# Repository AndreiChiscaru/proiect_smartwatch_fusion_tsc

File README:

# InkTime - Open Source Smartwatch 

Acest repository conține fișierele de design hardware (faza EVT) pentru **InkTime**, un smartwatch accesibil și open-source, bazat pe microcontrolerul nRF52840. Proiectul a fost dezvoltat de la specificații la PCB asamblat, incluzând schema electrică, design-ul plăcii și integrarea componentelor mecanice în carcasa 3D personalizată.

---

## 1. Diagrama Bloc a Sistemului

*(Notă: Arhitectura de bază folosește nRF52840 ca unitate centrală, comunicând periferic cu senzorii și display-ul, având un management de putere dedicat.)*

---

## 2. Descrierea Funcționalității Hardware

Sistemul este construit în jurul SoC-ului **nRF52840**, ales pentru conectivitatea Bluetooth Low Energy (BLE) și eficiența energetică excelentă.

**Module și Interfețe Integrate:**
* **Display E-Paper:** Conectat la microcontroler prin interfața **SPI** (MOSI, SCK, CS), asigurând un consum extrem de redus de energie, consumând curent doar în timpul refresh-ului ecranului.
* **IMU (Senzor de mișcare):** Pentru detecția gesturilor (ex. ridicarea mâinii). Comunică exclusiv prin interfața **I2C** (SDA, SCL).
* **Feedback Haptic (Shaker):** Un motor de vibrații controlat printr-un pin **PWM/GPIO**, utilizat pentru notificări silențioase.
* **Interfață Utilizator:** 3 butoane fizice tip push-button conectate cu rezistențe de pull-up interne.
* **Managementul Energiei:** * Sistemul este alimentat de o baterie Li-Po lipită direct pe pad-urile plăcii (fără conector JST) pentru a respecta constrângerea de spațiu pe axa Z.
  * Încărcarea se face prin portul **USB-C** folosind un circuit dedicat de management al bateriei.
  * Tensiunea este stabilizată la **3V3** printr-un convertor LDO/DC-DC pentru restul circuitelor.

---

## 3. Maparea Pinilor (nRF52840 Pinout)

Mai jos este prezentată alocarea pinilor pentru componentele periferice principale, optimizată pentru a minimiza încrucișările de trasee pe PCB:

| Componentă / Modul | Pini nRF52840 utilizați | Funcție / Interfață |
| :--- | :--- | :--- |
| **Display E-Paper** | P0.13, P0.15, P0.17, P0.20, P0.22 | SPI (SCK, MOSI, CS, DC, RST) |
| **Senzor IMU** | P0.26, P0.27 | I2C (SDA, SCL) |
| **Buton 1 (Up)** | P1.13 | GPIO (Input Pull-up) |
| **Buton 2 (Select)** | P1.14 | GPIO (Input Pull-up) |
| **Buton 3 (Down)** | P1.15 | GPIO (Input Pull-up) |
| **Motor Vibrații (Shaker)**| P0.11 | GPIO (Output / PWM) |
| **Monitorizare Baterie**| P0.02 | ADC (Analog In) |

---

## 4. Bill of Materials (BOM) Extras

Lista componentelor principale utilizate în acest design:

| Componentă | Capsulă / Pachet | Funcție | Link Achiziție / Datasheet |
| :--- | :--- | :--- | :--- |
| **nRF52840-QIAA-R** | QFN-73 | Microcontroler principal (SoC) | [JLC Parts](https://jlcpcb.com/parts) |
| **LSM6DS3TR** | LGA-14 | IMU (Accelerometru + Giroscop) | [JLC Parts](https://jlcpcb.com/parts) |
| **BQ24040DSQR** | WSON-8 | IC Management Încărcare Baterie | [JLC Parts](https://jlcpcb.com/parts) |
| **AP2112K-3.3** | SOT-23-5 | Regulator Tensiune 3.3V (LDO) | [JLC Parts](https://jlcpcb.com/parts) |
| **Conector FPC** | 24-pin, 0.5mm | Conector Display E-Paper | [JLC Parts](https://jlcpcb.com/parts) |
| **Pasive (C, R)** | 0201 / 0402 | Decuplare (100nF) și Pull-up (10k) | [JLC Parts](https://jlcpcb.com/parts) |

---

## 5. Design Log & Decizii de Proiectare (Issue-uri Acceptate)

Pentru a respecta cerințele tehnice și deadline-ul etapei EVT, au fost luate următoarele decizii de design:

* **Structura PCB:** Placa are **grosimea impusă de 1mm** și a fost realizată pe 2 layere (Top și Bottom). Amplasarea componentelor a fost făcută exclusiv pe layer-ul TOP. S-a realizat un plan de masă continuu pe ambele layere, unite prin via stitching.
* **Reguli de Rutare:** Liniile de alimentare (VCC, 3V3, VBAT, VUSB) au fost rutate manual respectând grosimea de **0.3mm**. Semnalele de date au folosit grosimea de **0.15mm**, evitându-se unghiurile drepte.
* **Zona RF:** Sub antena Bluetooth de 2.4GHz s-a aplicat Polygon Pour Cutout pe toate straturile. Nu există plan de masă sau trasee sub antenă, pentru a preveni ecranarea.
* **[BUG ACCEPTAT] Erori DRC și Acoperire Autorouter (89.2%):** Datorită densității masive de componente din jurul portului USB și a limitărilor mecanice foarte stricte impuse de carcasa 3D (mufele și butoanele au coordonate fixe), s-au acceptat temporar mici erori de tip *Overlap/Clearance* la condensatoarele 0201 aferente decuplării. Din același motiv de spațiu fizic limitat, Autorouter-ul a atins o acoperire maximă de 89.2%. Am decis să păstrez aceste câteva trasee nerutate pe Top în loc să mut componente pe Bottom, pentru a nu complica masiv viitorul proces de asamblare (Pick & Place pe ambele fețe crește mult costurile). Aceste conexiuni vor fi optimizate manual în sprint-ul pentru DVT.

---

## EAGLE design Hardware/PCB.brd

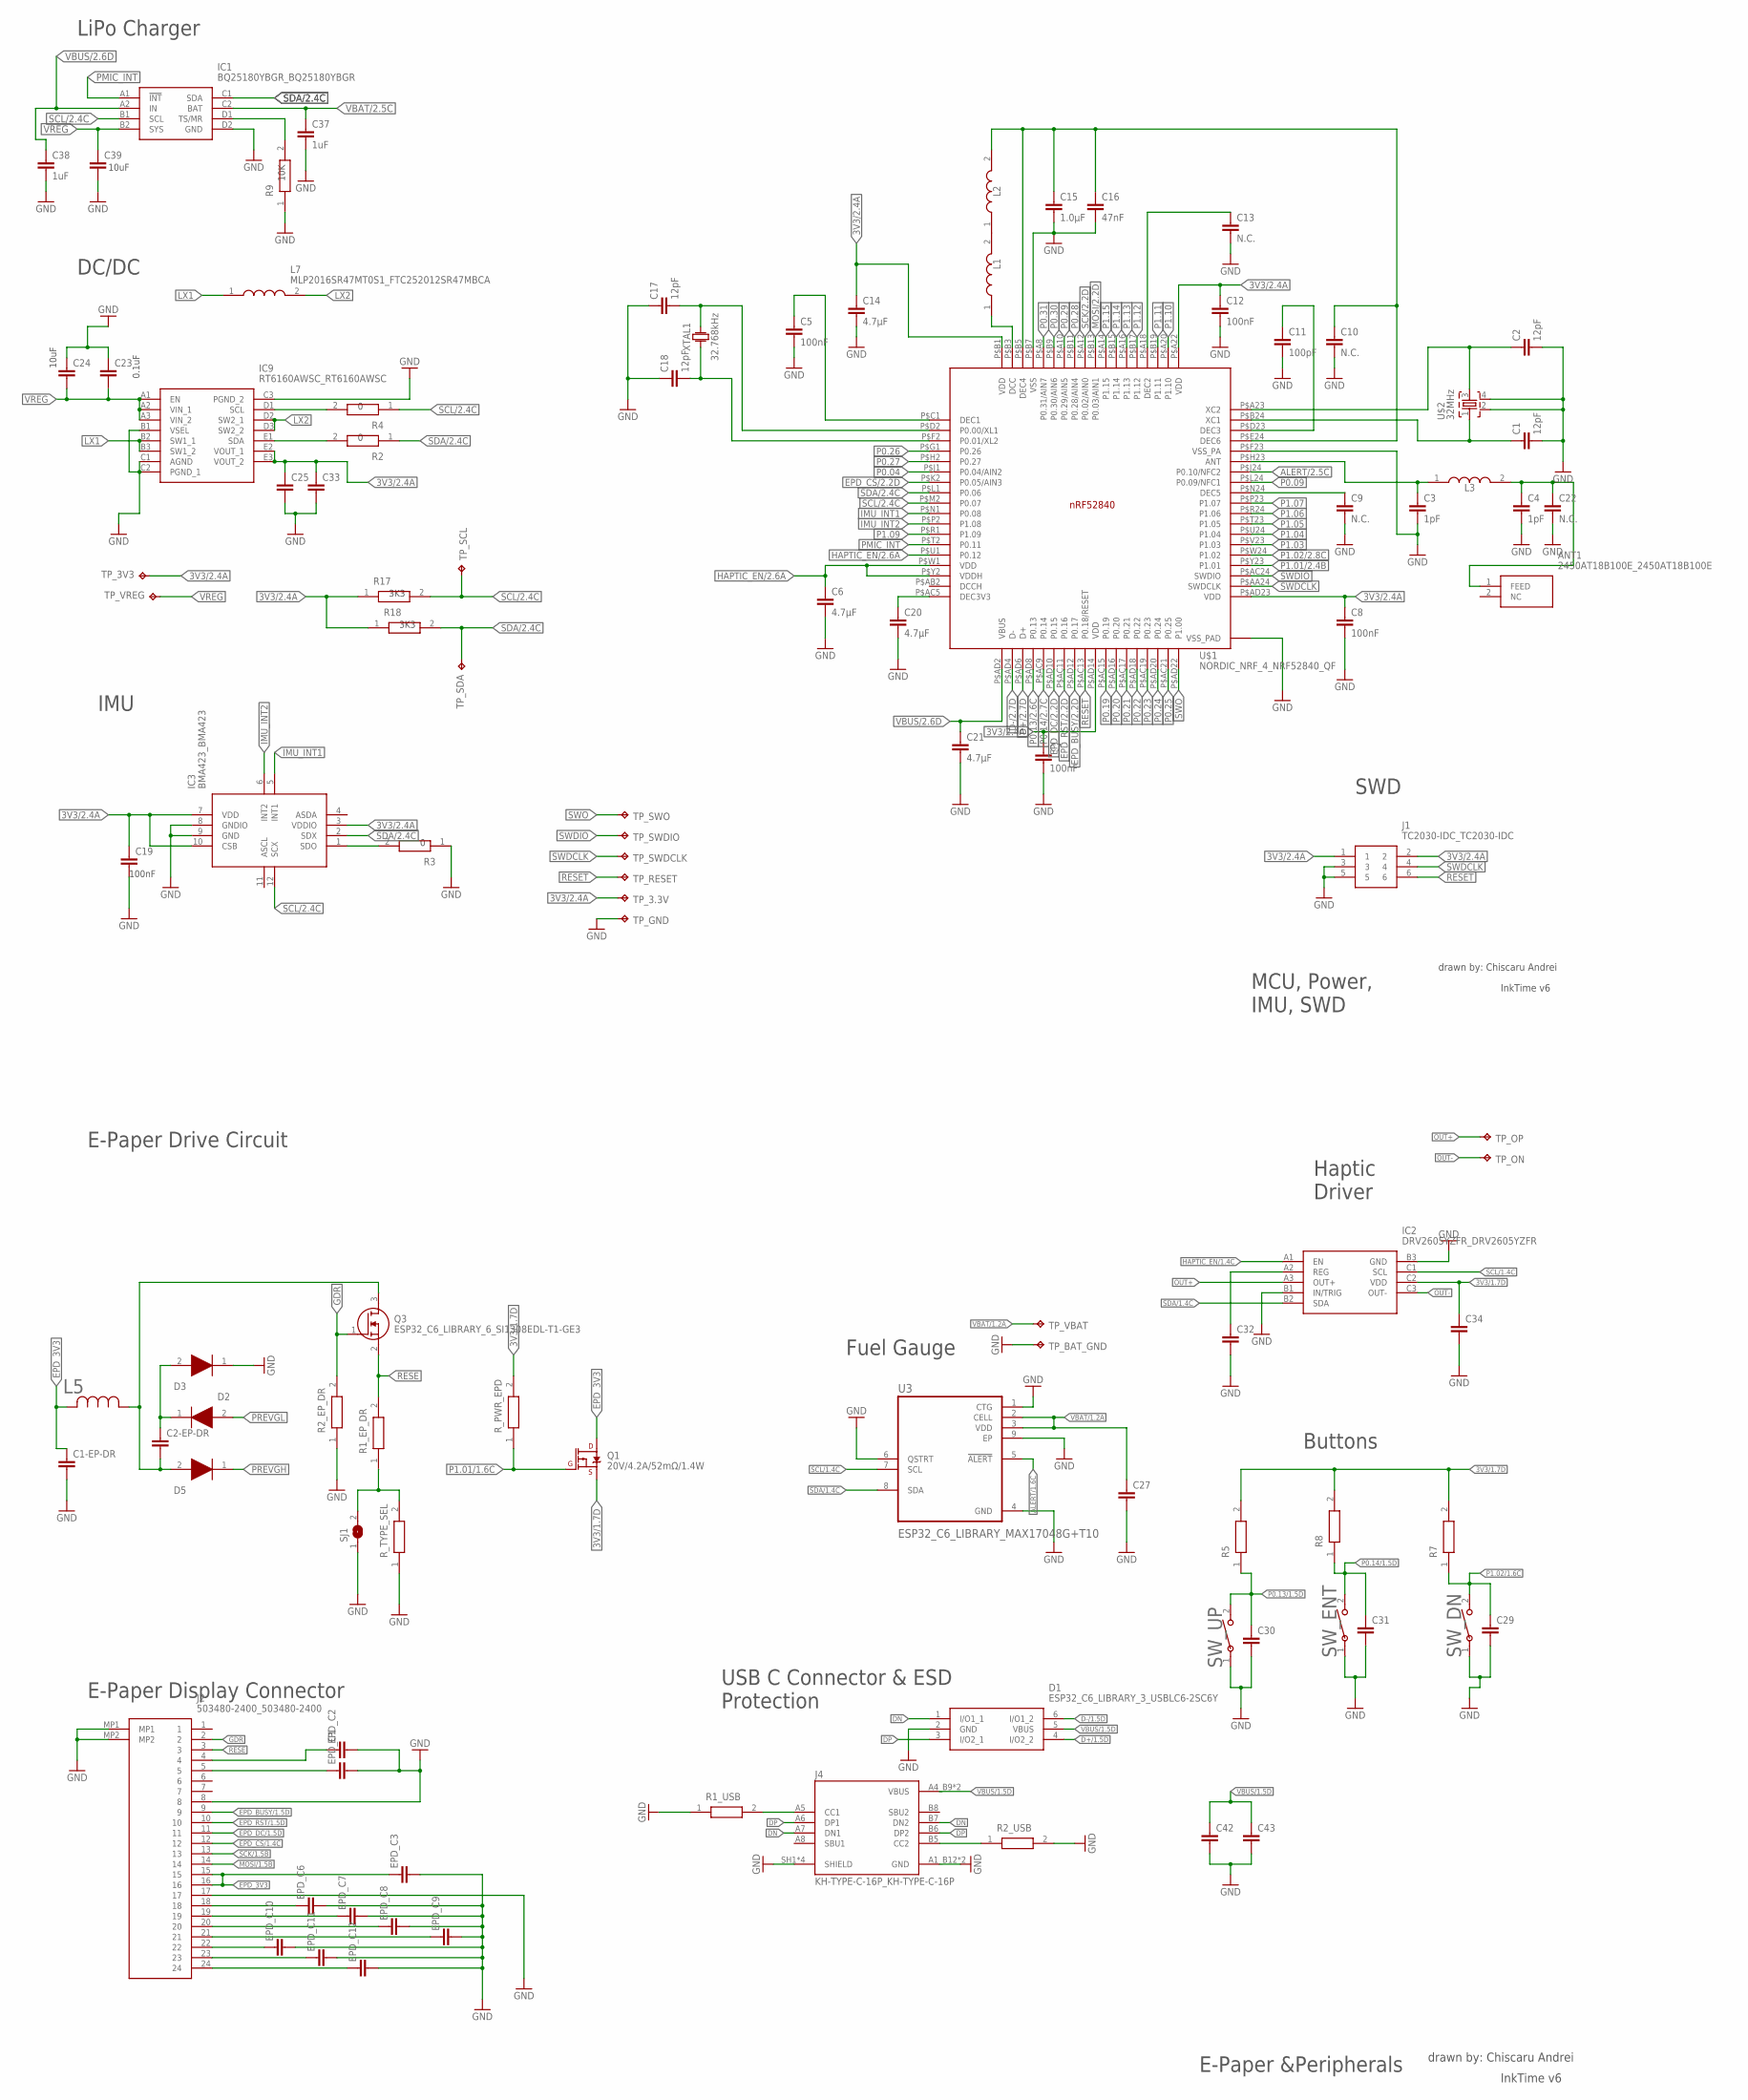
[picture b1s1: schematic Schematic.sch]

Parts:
ANT1: 2450AT18B100E_2450AT18B100E; 2450AT18B100E_ANTC3216X140N
C1, C2, C17, C18: 12pF; NORDIC_NRF_3_RESC0201_L
C1-EP-DR, C24, C39: 10uF; NORDIC_NRF_3_RESC0201_L
C2-EP-DR: 4.7uF/25V; NORDIC_NRF_3_RESC0201_L
C3, C4: 1pF; NORDIC_NRF_3_RESC0201_L
C5, C7, C8, C12, C19: 100nF; NORDIC_NRF_3_RESC0201_L
C6, C14, C20, C21: 4.7µF; NORDIC_NRF_3_RESC0201_L
C9, C10, C13, C22: N.C.; NORDIC_NRF_3_RESC0201_L
C11: 100pF; NORDIC_NRF_3_RESC0201_L
C15: 1.0µF; NORDIC_NRF_3_RESC0201_L
C16: 47nF; NORDIC_NRF_3_RESC0201_L
C23, C27, C34, C42: 0.1uF; NORDIC_NRF_3_RESC0201_L
C25, C33: 22uF; NORDIC_NRF_3_RESC0201_L
C29, C30, C31, C32, C37, C38: 1uF; NORDIC_NRF_3_RESC0201_L
C43: 4.7uF; NORDIC_NRF_3_RESC0201_L
D1: ESP32_C6_LIBRARY_3_USBLC6-2SC6Y; ESP32_C6_LIBRARY_3_SOT95P280X145-6N
D2, D3, D5: ESP32_C6_LIBRARY_5_MBR0530; ESP32_C6_LIBRARY_5_SOD3716X135N
EPD_C1, EPD_C2, EPD_C6, EPD_C7, EPD_C8, EPD_C9, EPD_C10, EPD_C11, EPD_C12: 1uF/50V; NORDIC_NRF_3_RESC0201_L
EPD_C3: 0.1uF/50V; NORDIC_NRF_3_RESC0201_L
IC1: BQ25180YBGR_BQ25180YBGR; BQ25180YBGR_BGA8C40P2X4_100X155X50
IC2: DRV2605YZFR_DRV2605YZFR; DRV2605YZFR_BGA9C50P3X3_144X144X62
IC3: BMA423_BMA423
IC9: RT6160AWSC_RT6160AWSC; RT6160AWSC_BGA15C40P3X5_140X230X60
J1: TC2030-IDC_TC2030-IDC; TC2030-IDC_TC2030IDC
J2: 503480-2400_503480-2400; 503480-2400_5034802400
J4: KH-TYPE-C-16P_KH-TYPE-C-16P; KH-TYPE-C-16P_KINGHELM_KH-TYPE-C-16P
L1: 10µH; MLP2016SR47MT0S1_INDC2016X100N
L2: 15nH; MLP2016SR47MT0S1_INDC2016X100N
L3: 3.9nH; MLP2016SR47MT0S1_INDC2016X100N
L5: 68uH; ESP32_C6_LIBRARY_2_IND_4828-WE-TPC_WRE
L7: MLP2016SR47MT0S1_FTC252012SR47MBCA; MLP2016SR47MT0S1_INDC2016X100N
Q1: 20V/4.2A/52mΩ/1.4W; ESP32_C6_LIBRARY_4_ESP32_C6_LIBRARY_4_ESP32_C6_LIBRARY_4_ES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
Q3: ESP32_C6_LIBRARY_6_SI1308EDL-T1-GE3; ESP32_C6_LIBRARY_6_SOT65P210X110-3N
R1_EP_DR: 0.47; CPF0201D7K68C1_0201
R1_USB, R2_USB: 5K1; CPF0201D7K68C1_0201
R2, R3, R4: 0; CPF0201D7K68C1_0201
R2_EP_DR, R5, R7, R8, R9: 10K; CPF0201D7K68C1_0201
R17, R18: 3K3; CPF0201D7K68C1_0201
R_PWR_EPD: 10K; CPF0201D7K68C1_0201
R_TYPE_SEL: 2.2; CPF0201D7K68C1_0201
SJ1: ESP32_C6_LIBRARY_7_JUMPER_SJ
SW_DN: 2025-10-22_07-23-44_LIBRARY_EVP-AKE31ASW_EVP-AKE3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; 2025-10-22_07-23-44_LIBRARY_SW_EVP-AKE31A_PAN
SW_ENT: 2025-10-22_07-23-44_LIBRARY_EVP-AKE31ASW_EVP-AKE3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; 2025-10-22_07-23-44_LIBRARY_SW_EVP-AKE31A_PAN
SW_UP: 2025-10-22_07-23-44_LIBRARY_EVP-AKE31ASW_EVP-AKE3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; 2025-10-22_07-23-44_LIBRARY_SW_EVP-AKE31A_PAN
TP_3.3V, TP_3V3: HECTOR_WATCH_1_TPTP20R; HECTOR_WATCH_1_TP20R
TP_BAT_GND: HECTOR_WATCH_1_TPTP20R; HECTOR_WATCH_1_TP20R
TP_GND: HECTOR_WATCH_1_TPTP20R; HECTOR_WATCH_1_TP20R
TP_ON: HECTOR_WATCH_1_TPTP20R; HECTOR_WATCH_1_TP20R
TP_OP: HECTOR_WATCH_1_TPTP20R; HECTOR_WATCH_1_TP20R
TP_RESET: HECTOR_WATCH_1_TPTP20R; HECTOR_WATCH_1_TP20R
TP_SCL: HECTOR_WATCH_1_TPTP20R; HECTOR_WATCH_1_TP20R
TP_SDA: HECTOR_WATCH_1_TPTP20R; HECTOR_WATCH_1_TP20R
TP_SWDCLK: HECTOR_WATCH_1_TPTP20R; HECTOR_WATCH_1_TP20R
TP_SWDIO: HECTOR_WATCH_1_TPTP20R; HECTOR_WATCH_1_TP20R
TP_SWO: HECTOR_WATCH_1_TPTP20R; HECTOR_WATCH_1_TP20R
TP_VBAT: HECTOR_WATCH_1_TPTP20R; HECTOR_WATCH_1_TP20R
TP_VREG: HECTOR_WATCH_1_TPTP20R; HECTOR_WATCH_1_TP20R
U3: ESP32_C6_LIBRARY_MAX17048G+T10; ESP32_C6_LIBRARY_SON50P200X200X80-9N
U$1: NORDIC_NRF_4_NRF52840_QF; NORDIC_NRF_4_AQFN50P700X700X85_HS-74N
U$2: 32MHz; NORDIC_NRF_BT-XTAL_2016_N
XTAL1: 32.768kHz; XTAL_ABS07-32.768KHZ-T

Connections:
3V3/1.7D: C34.1, IC2.C2 (VDD), Q1.2 (S), R5.2, R7.2, R8.2, R_PWR_EPD.2
3V3/2.4A: C7.1, C8.1, C12.1, C14.1, C19.1, C25.1, C33.1, IC3.3 (VDDIO), IC3.7 (VDD), IC3.10 (CSB), IC9.E2 (VOUT_1), IC9.E3 (VOUT_2), J1.1, R17.1, R18.1, TP_3.3V.TP, TP_3V3.TP, U$1.P$A22 (VDD), U$1.P$AD14 (VDD), U$1.P$AD23 (VDD), U$1.P$B1 (VDD)
ALERT/1.6C: U3.5 (!ALERT)
ALERT/2.5C: U$1.P$J24 (P0.10/NFC2)
D+/1.5D: D1.4 (I/O2_2)
D+/2.7D: U$1.P$AD6 (D+)
D-/1.5D: D1.6 (I/O1_2)
D-/2.7D: U$1.P$AD4 (D-)
DN: D1.1 (I/O1_1), J4.A7 (DN1), J4.B7 (DN2)
DP: D1.3 (I/O2_1), J4.A6 (DP1), J4.B6 (DP2)
EPD_3V3: C1-EP-DR.1, EPD_C3.1, J2.15, J2.16, L5.2, Q1.3 (D)
EPD_BUSY/1.5D: J2.9
EPD_BUSY/2.2D: U$1.P$AD12 (P0.17)
EPD_CS/1.4C: J2.12
EPD_CS/2.2D: U$1.P$K2 (P0.05/AIN3)
EPD_DC/1.5D: J2.11
EPD_DC/2.2D: U$1.P$AD10 (P0.15)
EPD_RST/1.5D: J2.10
EPD_RST/2.2D: U$1.P$AC11 (P0.16)
GDR: J2.2, Q3.1 (G), R2_EP_DR.2
GND: C1.2, C1-EP-DR.2, C2.2, C3.2, C4.2, C5.2, C6.2, C7.2, C8.2, C9.2, C10.2, C11.2, C12.2, C13.2, C14.2, C15.2, C16.2, C17.1, C18.1, C19.2, C20.2, C21.2, C22.2, C23.1, C24.1, C25.2, C27.2, C29.2, C30.2, C31.2, C32.2, C33.2, C34.2, C37.2, C38.2, C39.2, C42.2, C43.2, D1.2 (GND), D3.1 (K), EPD_C1.2, EPD_C2.2, EPD_C3.2, EPD_C6.2, EPD_C7.2, EPD_C8.2, EPD_C9.2, EPD_C10.2, EPD_C11.2, EPD_C12.2, IC1.D2 (GND), IC2.B1 (IN/TRIG), IC2.B3 (GND), IC3.8 (GNDIO), IC3.9 (GND), IC9.B1 (VSEL), IC9.C1 (AGND), IC9.C2 (PGND_1), IC9.C3 (PGND_2), J1.3, J1.5, J2.8, J2.17, J2.MP1, J2.MP2, J4.A1_B12 (GND), J4.A12_B1 (GND), J4.SH1 (SHIELD), J4.SH2 (SHIELD), J4.SH3 (SHIELD), J4.SH4 (SHIELD), R1_USB.1, R2_EP_DR.1, R2_USB.2, R3.1, R9.1, R_TYPE_SEL.1, SJ1.1, SW_DN.1, SW_ENT.1, SW_UP.1, TP_BAT_GND.TP, TP_GND.TP, U3.1 (CTG), U3.4 (GND), U3.6 (QSTRT), U3.9 (EP), U$1.P$74 (VSS_PAD), U$1.P$75 (VSS_PAD), U$1.P$76 (VSS_PAD), U$1.P$77 (VSS_PAD), U$1.P$78 (VSS_PAD), U$1.P$79 (VSS_PAD), U$1.P$80 (VSS_PAD), U$1.P$81 (VSS_PAD), U$1.P$82 (VSS_PAD), U$1.P$83 (VSS_PAD), U$1.P$84 (VSS_PAD), U$1.P$85 (VSS_PAD), U$1.P$86 (VSS_PAD), U$1.P$87 (VSS_PAD), U$1.P$88 (VSS_PAD), U$1.P$89 (VSS_PAD), U$1.P$90 (VSS_PAD), U$1.P$B7 (VSS), U$1.P$F23 (VSS_PA), U$2.2, U$2.4
HAPTIC_EN/1.4C: IC2.A1 (EN)
HAPTIC_EN/2.6A: C6.1, U$1.P$U1 (P0.12), U$1.P$W1 (VDD), U$1.P$Y2 (VDDH)
IMU_INT1: IC3.5 (INT1), U$1.P$N1 (P0.08)
IMU_INT2: IC3.6 (INT2), U$1.P$P2 (P1.08)
LX1: IC9.B2 (SW1_1), IC9.B3 (SW1_2), L7.1
LX2: IC9.D2 (SW2_1), IC9.D3 (SW2_2), L7.2
MOSI/1.5B: J2.14
MOSI/2.2D: U$1.P$B13 (P0.03/AIN1)
unnamed: EPD_C2.1, J2.4
unnamed: L1.1, U$1.P$B3 (DCC)
unnamed: IC1.D1 (TS/MR), R9.2
unnamed: C10.1, C15.1, C16.1, L2.2, U$1.P$B5 (DEC4), U$1.P$E24 (DEC6)
unnamed: IC9.E1 (SDA), R2.2
unnamed: EPD_C1.1, J2.5
unnamed: IC9.D1 (SCL), R4.2
unnamed: J4.A5 (CC1), R1_USB.2
unnamed: R1_EP_DR.1, R_TYPE_SEL.2, SJ1.2
unnamed: EPD_C6.1, J2.18
unnamed: IC3.1 (SDO), R3.2
unnamed: EPD_C7.1, J2.19
unnamed: EPD_C8.1, J2.20
unnamed: C2-EP-DR.2, D5.2 (A), L5.1, Q3.3 (D)
unnamed: C2-EP-DR.1, D2.1 (K), D3.2 (A)
unnamed: EPD_C9.1, J2.21
unnamed: EPD_C10.1, J2.22
unnamed: EPD_C11.1, J2.23
unnamed: C13.1, U$1.P$A18 (DEC2)
unnamed: EPD_C12.1, J2.24
unnamed: J4.B5 (CC2), R2_USB.1
unnamed: L1.2, L2.1
unnamed: C32.1, IC2.A2 (REG)
unnamed: C11.1, U$1.P$D23 (DEC3)
unnamed: C9.1, U$1.P$N24 (DEC5)
unnamed: C20.1, U$1.P$AC5 (DEC3V3)
unnamed: C5.1, U$1.P$C1 (DEC1)
unnamed: C2.1, U$1.P$A23 (XC2), U$2.3
unnamed: C1.1, U$1.P$B24 (XC1), U$2.1
unnamed: C3.1, L3.1, U$1.P$H23 (ANT)
unnamed: C17.2, U$1.P$D2 (P0.00/XL1), XTAL1.2
unnamed: ANT1.1 (FEED), C4.1, C22.1, L3.2
unnamed: C18.2, U$1.P$F2 (P0.01/XL2), XTAL1.1
OUT+: IC2.A3 (OUT+), TP_OP.TP
OUT-: IC2.C3 (OUT-), TP_ON.TP
P0.04: U$1.P$J1 (P0.04/AIN2)
P0.09: U$1.P$L24 (P0.09/NFC1)
P0.13/1.5D: C30.1, R5.1, SW_UP.2
P0.13/2.6C: U$1.P$AD8 (P0.13)
P0.14/1.5D: C31.1, R8.1, SW_ENT.2
P0.14/2.7C: U$1.P$AC9 (P0.14)
P0.19: U$1.P$AC15 (P0.19)
P0.20: U$1.P$AD16 (P0.20)
P0.21: U$1.P$AC17 (P0.21)
P0.22: U$1.P$AD18 (P0.22)
P0.23: U$1.P$AC19 (P0.23)
P0.24: U$1.P$AD20 (P0.24)
P0.25: U$1.P$AC21 (P0.25)
P0.26: U$1.P$G1 (P0.26)
P0.27: U$1.P$H2 (P0.27)
P0.28: U$1.P$B11 (P0.28/AIN4)
P0.29: U$1.P$A10 (P0.29/AIN5)
P0.30: U$1.P$B9 (P0.30/AIN6)
P0.31: U$1.P$A8 (P0.31/AIN7)
P1.01/1.6C: Q1.1 (G), R_PWR_EPD.1
P1.01/2.4B: U$1.P$Y23 (P1.01)
P1.02/1.6C: C29.1, R7.1, SW_DN.2
P1.02/2.8C: U$1.P$W24 (P1.02)
P1.03: U$1.P$V23 (P1.03)
P1.04: U$1.P$U24 (P1.04)
P1.05: U$1.P$T23 (P1.05)
P1.06: U$1.P$R24 (P1.06)
P1.07: U$1.P$P23 (P1.07)
P1.09: U$1.P$R1 (P1.09)
P1.10: U$1.P$A20 (P1.10)
P1.11: U$1.P$B19 (P1.11)
P1.12: U$1.P$B17 (P1.12)
P1.13: U$1.P$A16 (P1.13)
P1.14: U$1.P$B15 (P1.14)
P1.15: U$1.P$A14 (P1.15)
PMIC_INT: IC1.A1 (!INT), U$1.P$T2 (P0.11)
PREVGH: D5.1 (K)
PREVGL: D2.2 (A)
RESE: J2.3, Q3.2 (S), R1_EP_DR.2
RESET: J1.6, TP_RESET.TP, U$1.P$AC13 (P0.18/RESET)
SCK/1.5B: J2.13
SCK/2.2D: U$1.P$A12 (P0.02/AIN0)
SCL/1.4C: IC2.C1 (SCL), U3.7 (SCL)
SCL/2.4C: IC1.B1 (SCL), IC3.12 (SCX), R4.1, R17.2, TP_SCL.TP, U$1.P$M2 (P0.07)
SDA/1.4C: IC2.B2 (SDA), U3.8 (SDA)
SDA/2.4C: IC1.C1 (SDA), IC3.2 (SDX), R2.1, R18.2, TP_SDA.TP, U$1.P$L1 (P0.06)
SWDCLK: J1.4, TP_SWDCLK.TP, U$1.P$AA24 (SWDCLK)
SWDIO: TP_SWDIO.TP, U$1.P$AC24 (SWDIO)
SWO: TP_SWO.TP, U$1.P$AD22 (P1.00)
VBAT/1.2A: C27.1, TP_VBAT.TP, U3.2 (CELL), U3.3 (VDD)
VBAT/2.5C: C37.1, IC1.C2 (BAT)
VBUS/1.5D: C42.1, C43.1, D1.5 (VBUS), J4.A4_B9 (VBUS), J4.A9_B4 (VBUS)
VBUS/2.6D: C21.1, C38.1, IC1.A2 (IN), U$1.P$AD2 (VBUS)
VREG: C23.2, C24.2, C39.1, IC1.B2 (SYS), IC9.A1 (EN), IC9.A2 (VIN_1), IC9.A3 (VIN_2), TP_VREG.TP

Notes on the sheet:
LiPo Charger
10uF
10K
DC/DC
3K3
0.1uF
IMU
100nF
SWD
MCU, Power, IMU, SWD
drawn by: Chiscaru Andrei
InkTime v6
E-Paper Drive Circuit
E-Paper Display Connector
Haptic Driver
Fuel Gauge
Buttons
USB C Connector & ESD Protection
E-Paper &Peripherals

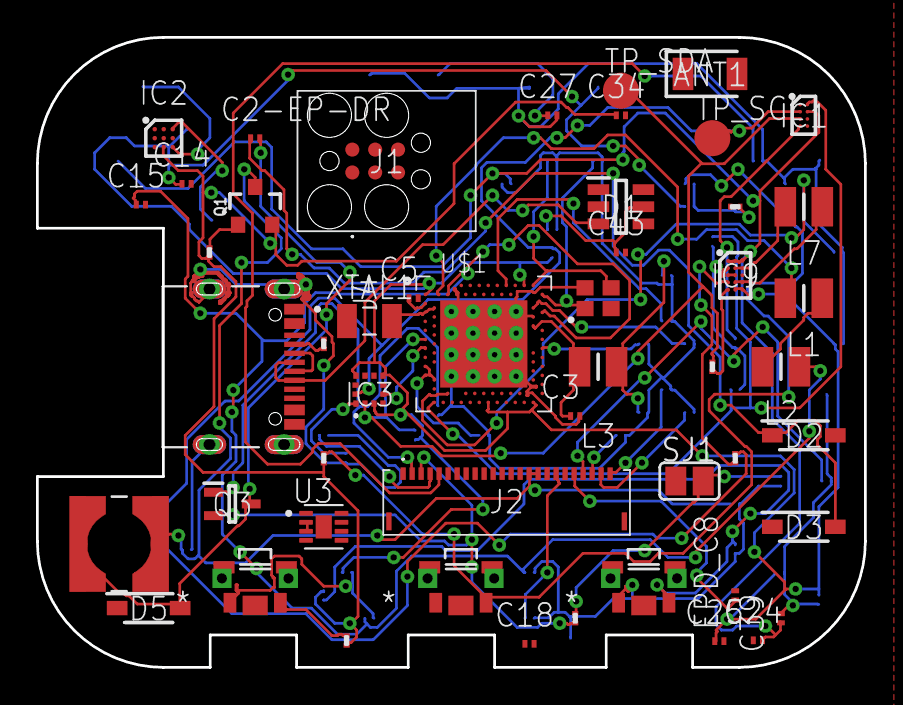
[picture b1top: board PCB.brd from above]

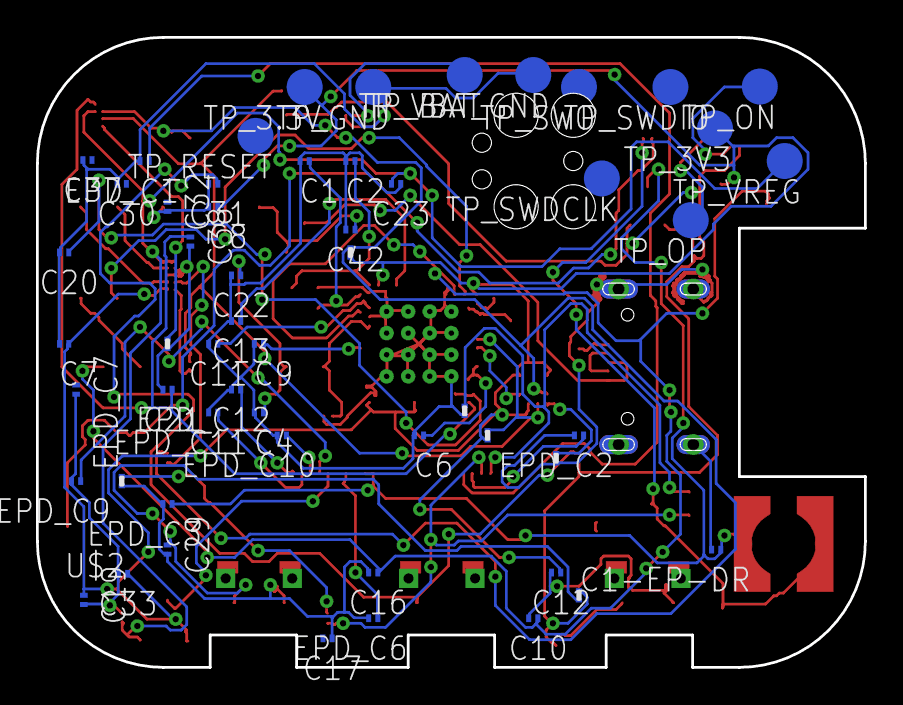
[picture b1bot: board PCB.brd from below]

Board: 2 copper layers, 46.0 x 35.0 mm, 105 parts (55 on the bottom side), 66 nets.

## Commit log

2026-04-09 Add README.md file

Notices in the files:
parts and their libraries:
COPYRIGHT: Copyright (C) 2024 Ultra Librarian. All rights reserved.
COPYRIGHT: Copyright (C) 2025 Ultra Librarian. All rights reserved.
